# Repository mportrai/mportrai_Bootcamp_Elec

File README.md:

# mportrai_Bootcamp_Elec

## Liste des composants utilises:
| **Reference**  | **Qty** | **Value** | **DNP** | **Excl. BOM** | **Excl. Board** | **Footprint** | **Datasheet** |
|----------------|-----|------------------------|-----|-----------|-------------|------------------------------------------------|---------------|
| C1, C2         | 2   | Condensateur 12 pF     |     |           |             | mportrai_footprints:CL10C120JB8NNNC            | [Datasheet](https://mm.digikey.com/Volume0/opasdata/d220001/medias/docus/658/CL10A105KB8NNNC_Spec.pdf) |
| C3, C4, C7     | 3   | Condensateur 100 nF    |     |           |             | mportrai_footprints:CC0603KRX7R9BB104          | [Datasheet](https://www.yageogroup.com/content/datasheet/asset/file/UPY-GPHC_X7R_6_3V-TO-250V) |
| C6             | 1   | Condensateur 1 uF      |     |           |             | mportrai_footprints:CL10A105KB8NNNC            | [Datasheet](https://mm.digikey.com/Volume0/opasdata/d220001/medias/docus/658/CL10A105KB8NNNC_Spec.pdf) |
| D1             | 1   | LED Green              |     |           |             | mportrai_footprints:TZ-P2-0603YGTCS1-0.6T      | [Datasheet](https://xonstorage.z8.web.core.windows.net/pdf/tuozhan_tzp20603ygtcs106t_apr22_xonlink.pdf) |
| D2             | 1   | LED Red                |     |           |             | mportrai_footprints:XL-1608SURC-06             | [Datasheet](https://mm.digikey.com/Volume0/opasdata/d220001/medias/docus/6472/5962_XL-1608SURC-06%20%20%200603%E7%BA%A20.6T.pdf) |
| J1, J2         | 2   | ~                      |     |           |             | mportrai_footprints:Connecteur_1               | [Datasheet]() |
| J3             | 1   | FTDI                   |     |           |             | mportrai_footprints:Connecteur_2               | [Datasheet]() |
| R1             | 1   | Résistance 330 Ω       |     |           |             | mportrai_footprints:0603WAF3300T5E             | [Datasheet](https://www.lcsc.com/datasheet/C23138.pdf) |
| R2, R3         | 2   | Résistance 10 kΩ       |     |           |             | mportrai_footprints:RC0603FR-0710KL            | [Datasheet](https://www.yageogroup.com/content/datasheet/asset/file/PYU-RC_GROUP_51_ROHS_L) |
| SW1            | 1   | SW_Push                |     |           |             | mportrai_footprints:B3U-1000P                  | [Datasheet](https://omronfs.omron.com/en_US/ecb/products/pdf/en-b3u.pdf) |
| U1             | 1   | ATmega328P-A           |     |           |             | mportrai_footprints:ATMEGA328P-AU              | [Datasheet](https://ww1.microchip.com/downloads/en/DeviceDoc/ATmega48A-PA-88A-PA-168A-PA-328-P-DS-DS40002061B.pdf) |
| Y1             | 1   | Cristal 16 MHz         |     |           |             | mportrai_footprints:X322516MLB4SI              | [Datasheet](https://jlcpcb.com/api/file/downloadByFileSystemAccessId/8588879072148017152) |

## Pin Layout
| **PIN number** | **Label Connecteur J1** | **Label Connecteur J2** | **Label Connecteur J3** |
|----------------|-------------------------|-------------------------|-------------------------|
| 1 | D9 | RAW | DTR |
| 2 | D8 | GND | TX0 |
| 3 | D7 | RST | RXI |
| 4 | D6 | VCC | VCC |
| 5 | D5 | A3 | GND |
| 6 | D4 | A2 | GND |
| 7 | D3 | A1 | x |
| 8 | D2 | A0 | x |
| 9 | GND | SCK | x |
| 10 | RST | MISO | x |
| 11 | RXI | MOSI | x |
| 12 | TX0 | D10 | x |

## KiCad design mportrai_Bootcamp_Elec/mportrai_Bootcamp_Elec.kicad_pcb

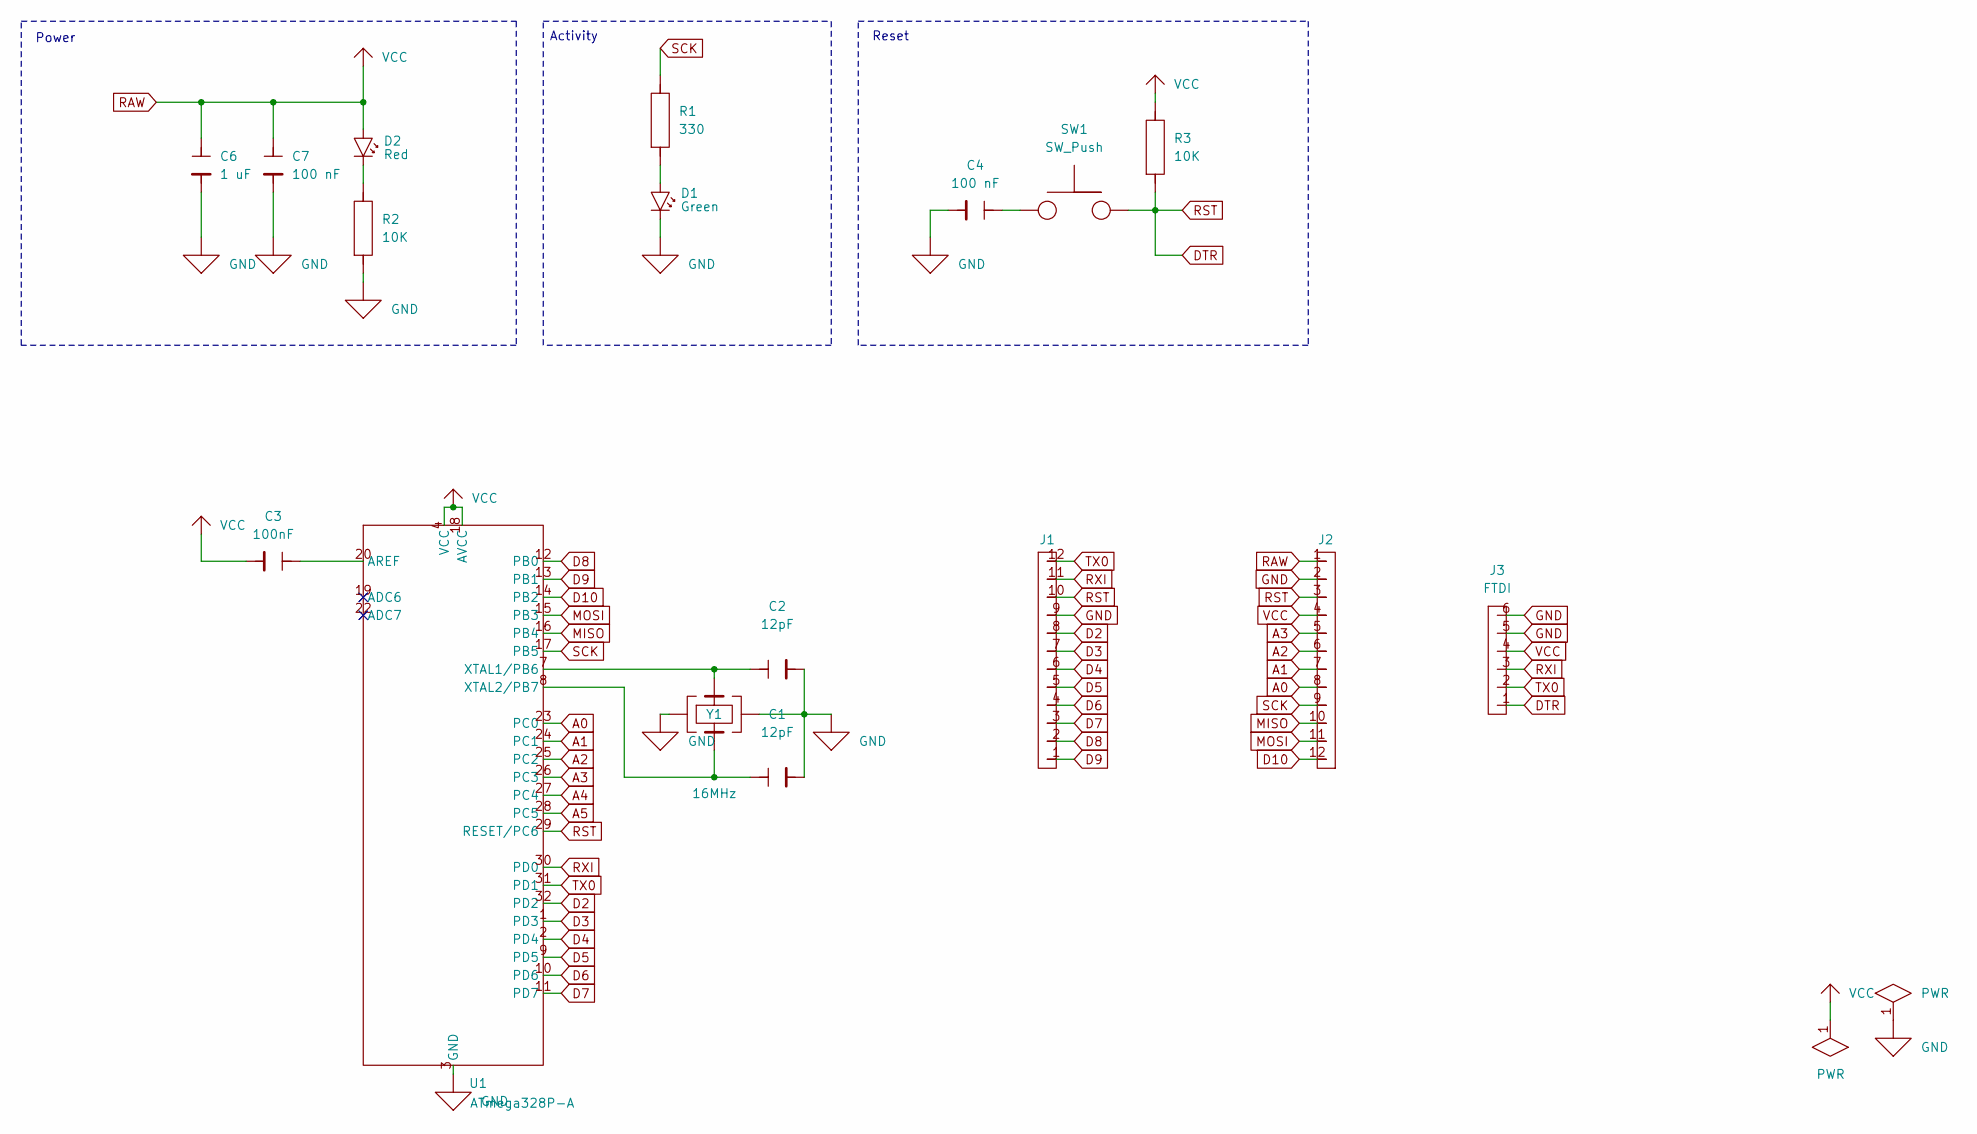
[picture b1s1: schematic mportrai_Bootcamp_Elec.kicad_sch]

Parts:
C1, C2: 12pF; CL10C120JB8NNNC
C3: 100nF; CC0603KRX7R9BB104
C4, C7: 100 nF; CC0603KRX7R9BB104
C6: 1 uF; CL10A105KB8NNNC
D1: Green; TZ-P2-0603YGTCS1-0.6T
D2: Red; XL-1608SURC-06
J1, J2: Connecteur_1
J3: FTDI; Connecteur_2
R1: 330; 0603WAF3300T5E
R2, R3: 10K; RC0603FR-0710KL
SW1: SW_Push; B3U-1000P
U1: ATmega328P-A; ATMEGA328P-AU
Y1: 16MHz; X322516MLB4SI

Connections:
A0: J2.8, U1.23 (PC0)
A1: J2.7, U1.24 (PC1)
A2: J2.6, U1.25 (PC2)
A3: J2.5, U1.26 (PC3)
A4: U1.27 (PC4)
A5: U1.28 (PC5)
D2: J1.8, U1.32 (PD2)
D3: J1.7, U1.1 (PD3)
D4: J1.6, U1.2 (PD4)
D5: J1.5, U1.9 (PD5)
D6: J1.4, U1.10 (PD6)
D7: J1.3, U1.11 (PD7)
D8: J1.2, U1.12 (PB0)
D9: J1.1, U1.13 (PB1)
D10: J2.12, U1.14 (PB2)
DTR: J1.10, J2.3, J3.1, R3.1, SW1.1, U1.29 (RESET/PC6)
MISO: J2.10, U1.16 (PB4)
MOSI: J2.11, U1.15 (PB3)
unnamed: C4.1, SW1.2
unnamed: D1.1, R1.1
unnamed: D2.2, R2.2
unnamed: C3.1, U1.20 (AREF)
unnamed: C2.1, U1.7 (XTAL1/PB6), Y1.1
unnamed: C1.1, U1.8 (XTAL2/PB7), Y1.3
RXI: J1.11, J3.3, U1.30 (PD0)
SCK: J2.9, R1.2, U1.17 (PB5)
TX0: J1.12, J3.2, U1.31 (PD1)

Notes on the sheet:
Reset
Activity
Power

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
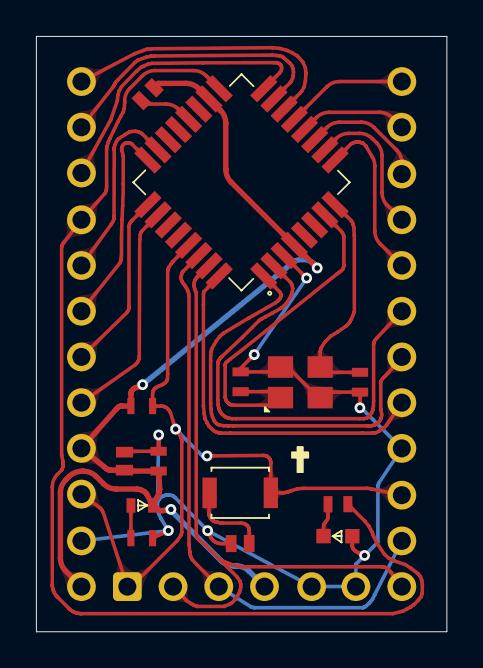
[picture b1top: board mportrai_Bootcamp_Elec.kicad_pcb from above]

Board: 2 copper layers, 22.8 x 33.1 mm, 17 parts (0 on the bottom side), 27 nets.

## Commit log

2025-11-23 Copie du projet pour rendu
2025-11-23 Une erreur syntaxe texte/URL parce que j'utilise pas trop ca, Oups
2025-11-24 modif sch-pcb, modif librairie * to mportrai_*, pinout
2025-11-27 modif du tableau Pin layout
2025-11-30 non save
